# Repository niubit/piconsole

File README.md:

# PiConsole - Raspberry Pi Pico Retro Console

This repository has submodules. To clone add the `--recursive` option to the git clone command:

```
git clone --recursive https://github.com/niubit/piconsole.git
```

You can see a brief description (in spanish) in [this site](https://niubitbox.niubit.es/docs/niubitbox005/). A full description in english is available in [Instructables](https://www.instructables.com/PiConsole-Raspberry-Pi-Pico-Retro-Console/).

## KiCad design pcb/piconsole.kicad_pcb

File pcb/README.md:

Clonar con:

git clone --recursive git@bitbucket.org:niubit/piconsole_pcb.git

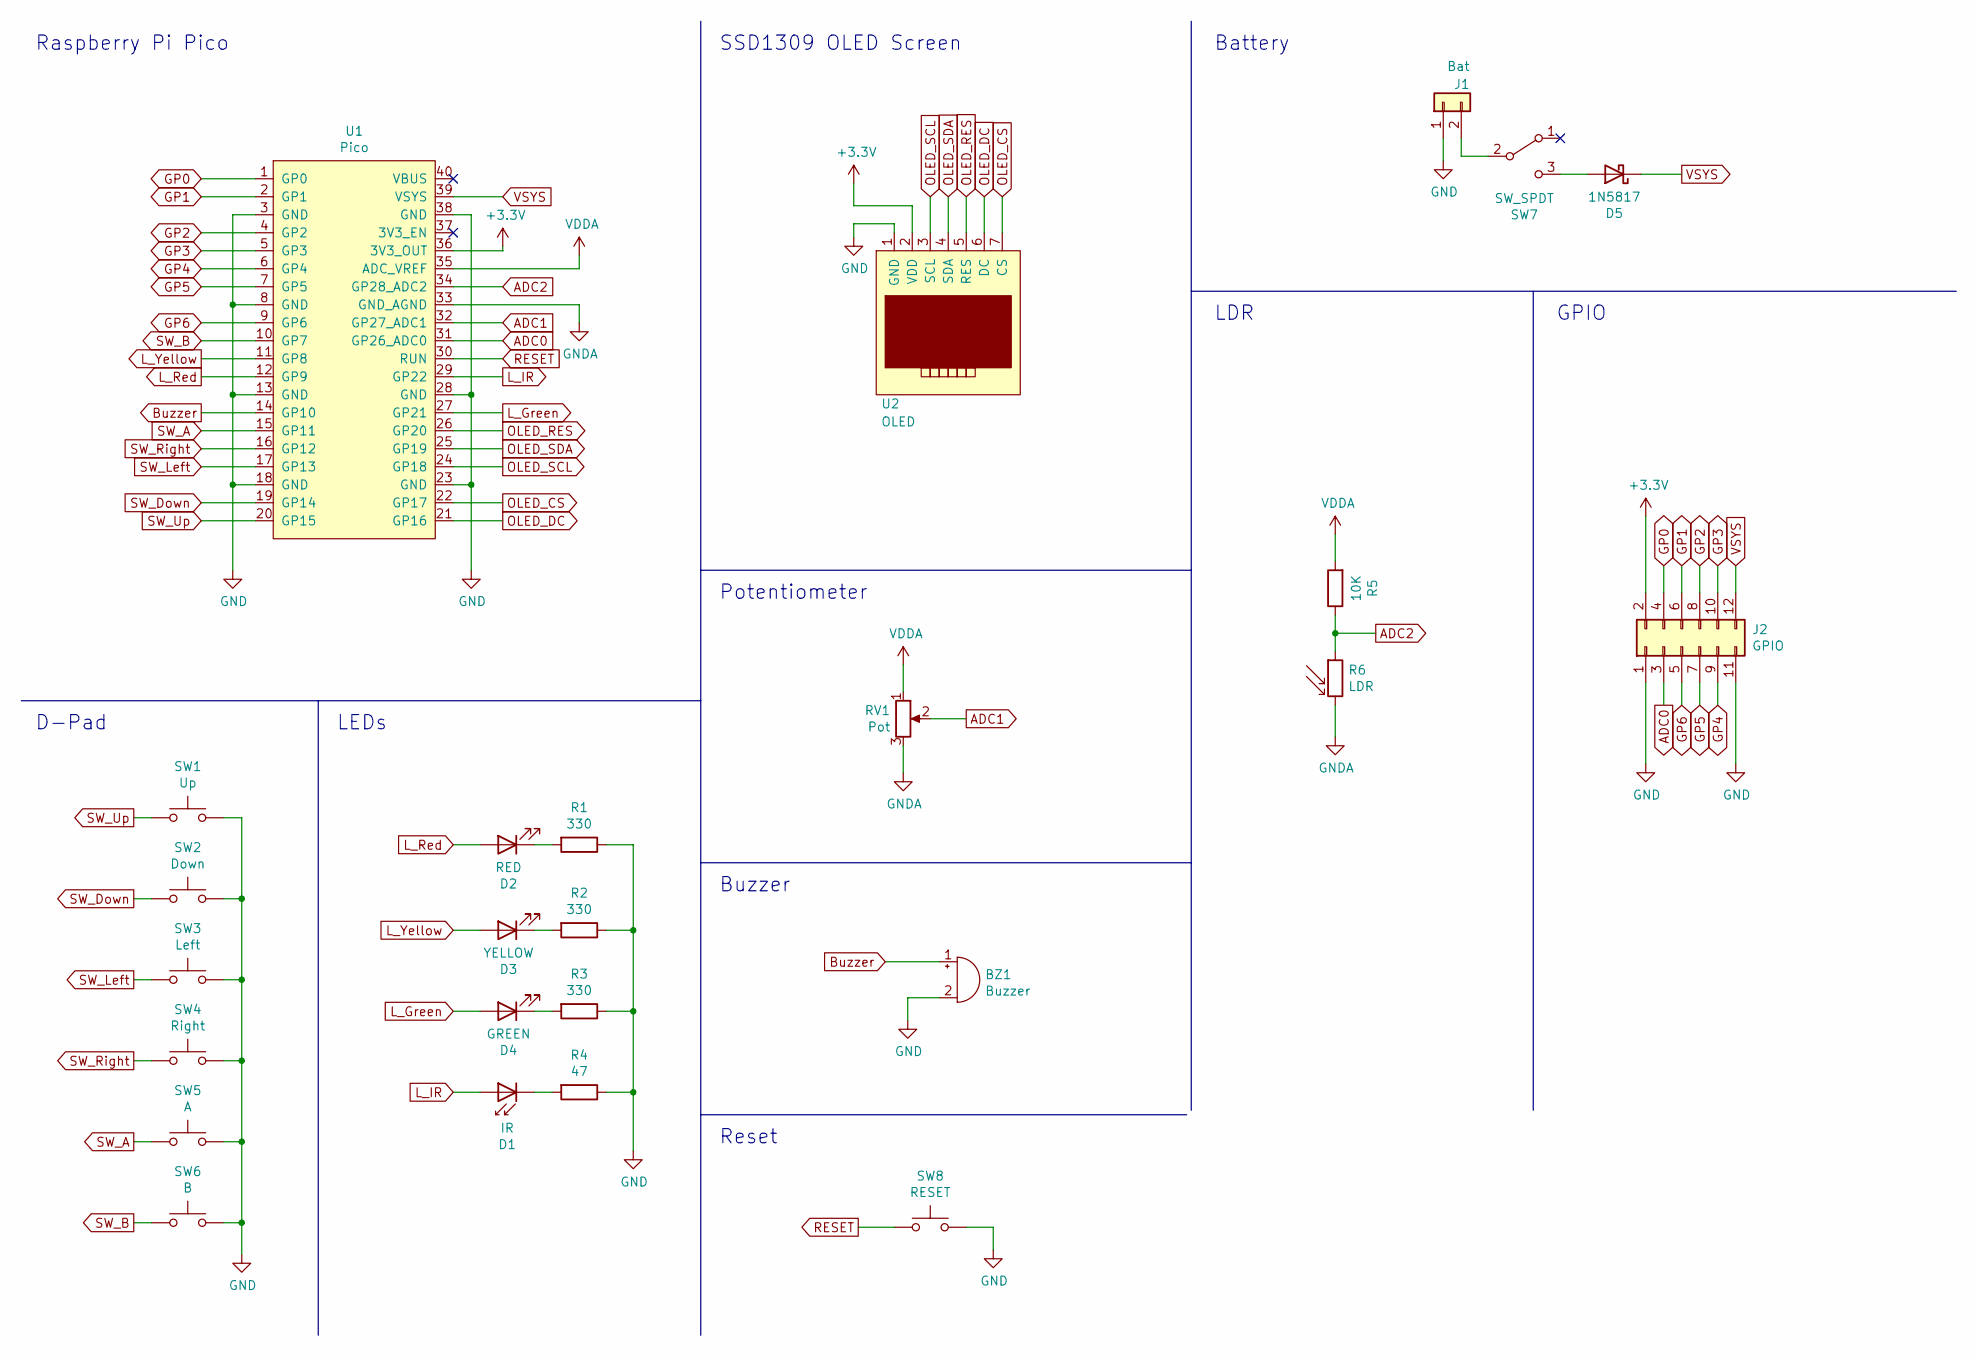
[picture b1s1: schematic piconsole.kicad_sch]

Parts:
BZ1: Buzzer; MagneticBuzzer_ProSignal_ABT-410-RC
D1: IR; LED_D5.0mm_IRGrey
D2: RED; LED_D5.0mm
D3: YELLOW; LED_D5.0mm
D4: GREEN; LED_D5.0mm
D5: 1N5817; D_DO-41_SOD81_P7.62mm_Horizontal
J1: Bat; PinHeader_1x02_P2.54mm_Vertical
J2: GPIO; PinSocket_2x06_P2.54mm_Horizontal
R1, R2, R3: 330; R_Axial_DIN0207_L6.3mm_D2.5mm_P10.16mm_Horizontal
R4: 47; R_Axial_DIN0207_L6.3mm_D2.5mm_P10.16mm_Horizontal
R5: 10K; R_Axial_DIN0207_L6.3mm_D2.5mm_P10.16mm_Horizontal
R6: LDR; R_LDR_5.0x4.1mm_P3mm_Vertical
RV1: Pot; Potentiometer_Alpha_RD901F-40-00D_Single_Vertical_mod
SW1: Up; SW_PUSH_8mm_2pin
SW2: Down; SW_PUSH_8mm_2pin
SW3: Left; SW_PUSH_8mm_2pin
SW4: Right; SW_PUSH_8mm_2pin
SW5: A; SW_PUSH_8mm_2pin
SW6: B; SW_PUSH_8mm_2pin
SW7: SW_SPDT; SW_SPDT_Angled
SW8: RESET; SW_PUSH_6mm
U1: Pico; raspberrypi-pico-module
U2: OLED; OLED-SSD1309-SPI

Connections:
+3V3: J2.2, U1.36 (3V3_OUT), U2.2 (VDD)
ADC0: J2.3, U1.31 (GP26_ADC0)
ADC1: RV1.2, U1.32 (GP27_ADC1)
ADC2: R5.1, R6.1, U1.34 (GP28_ADC2)
Buzzer: BZ1.1 (-), U1.14 (GP10)
GND: BZ1.2 (+), J1.1, J2.1, J2.11, R1.1, R2.1, R3.1, R4.1, SW1.2, SW2.2, SW3.2, SW4.2, SW5.2, SW6.2, SW8.2, U1.3 (GND), U1.8 (GND), U1.13 (GND), U1.18 (GND), U1.23 (GND), U1.28 (GND), U1.38 (GND), U2.1 (GND)
GNDA: R6.2, RV1.3, U1.33 (GND_AGND)
GP0: J2.4, U1.1 (GP0)
GP1: J2.6, U1.2 (GP1)
GP2: J2.8, U1.4 (GP2)
GP3: J2.10, U1.5 (GP3)
GP4: J2.9, U1.6 (GP4)
GP5: J2.7, U1.7 (GP5)
GP6: J2.5, U1.9 (GP6)
L_Green: D4.2 (A), U1.27 (GP21)
L_IR: D1.2 (A), U1.29 (GP22)
L_Red: D2.2 (A), U1.12 (GP9)
L_Yellow: D3.2 (A), U1.11 (GP8)
unnamed: D1.1 (K), R4.2
unnamed: D2.1 (K), R1.2
unnamed: D3.1 (K), R2.2
unnamed: D4.1 (K), R3.2
unnamed: D5.2 (A), SW7.3 (C)
unnamed: J1.2, SW7.2 (B)
OLED_CS: U1.22 (GP17), U2.7 (CS)
OLED_DC: U1.21 (GP16), U2.6 (DC)
OLED_RES: U1.26 (GP20), U2.5 (RES)
OLED_SCL: U1.24 (GP18), U2.3 (SCL)
OLED_SDA: U1.25 (GP19), U2.4 (SDA)
RESET: SW8.1, U1.30 (RUN)
SW_A: SW5.1, U1.15 (GP11)
SW_B: SW6.1, U1.10 (GP7)
SW_Down: SW2.1, U1.19 (GP14)
SW_Left: SW3.1, U1.17 (GP13)
SW_Right: SW4.1, U1.16 (GP12)
SW_Up: SW1.1, U1.20 (GP15)
VDDA: R5.2, RV1.1, U1.35 (ADC_VREF)
VSYS: D5.1 (K), J2.12, U1.39 (VSYS)

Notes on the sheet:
Buzzer
Potentiometer
LDR
Reset
LEDs
GPIO
D-Pad
SSD1309 OLED Screen
Raspberry Pi Pico
Battery

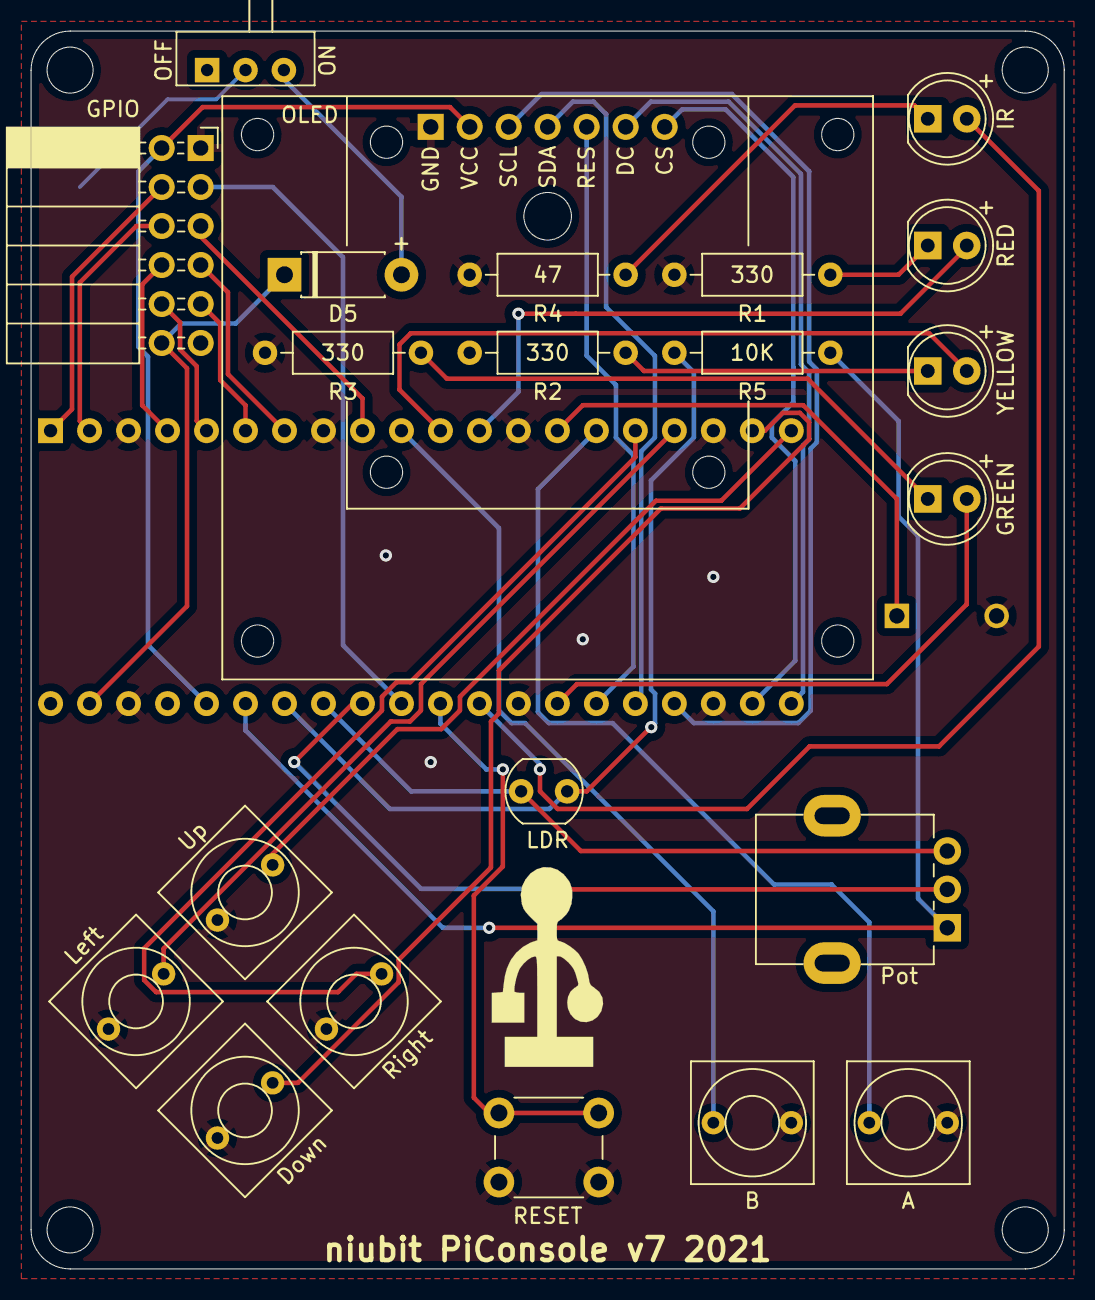
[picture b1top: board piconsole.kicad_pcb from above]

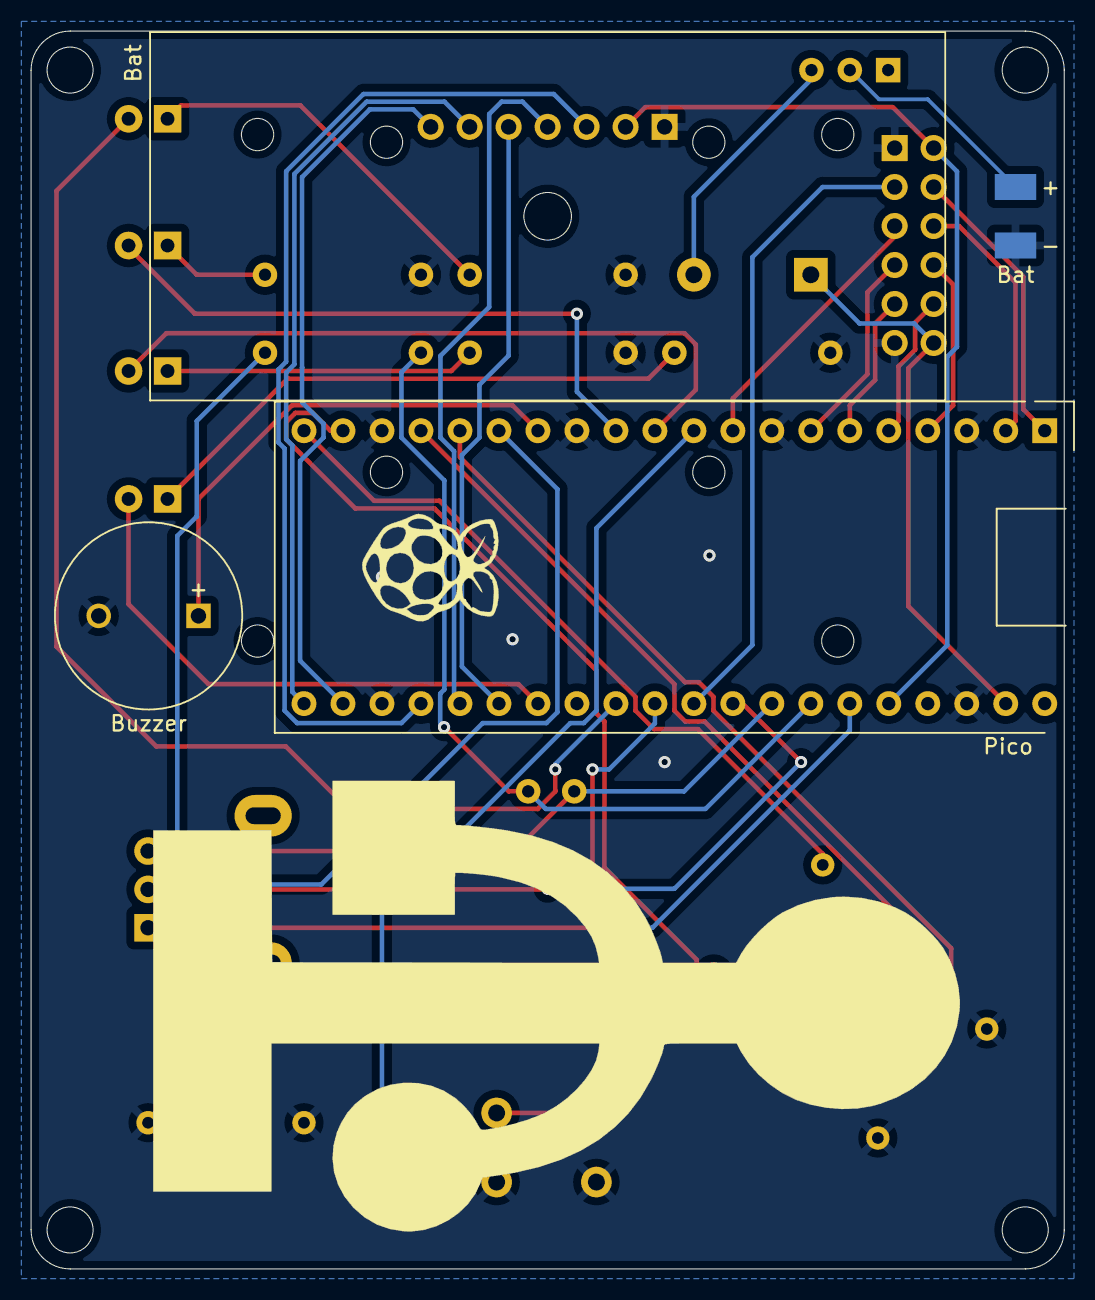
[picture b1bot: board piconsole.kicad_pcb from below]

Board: 2 copper layers, 67.3 x 80.6 mm, 25 parts (3 on the bottom side), 38 nets.

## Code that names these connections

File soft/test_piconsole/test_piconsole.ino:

#include <SPI.h>
#include <Wire.h>
#include <Adafruit_GFX.h>
#include <Adafruit_SSD1306.h>

#define SCREEN_WIDTH 128 // OLED display width, in pixels
#define SCREEN_HEIGHT 64 // OLED display height, in pixels

// Pins OLED
#define OLED_DC  16
#define OLED_CS  17
#define OLED_SCL 18
#define OLED_SDA 19
#define OLED_RES 20

// Pins LED
#define LED_YELLOW 8
#define LED_RED    9
#define LED_GREEN  21
#define LED_IR     22

// Pins Switch
#define SW_B     7
#define SW_A     11
#define SW_RIGHT 12
#define SW_LEFT  13
#define SW_DOWN  14
#define SW_UP    15

// Pins GPIO
#define GPIO_GP0     0
#define GPIO_GP1     1
#define GPIO_GP2     2
#define GPIO_GP3     3
#define GPIO_GP4     4
#define GPIO_GP5     5
#define GPIO_GP6     6
#define GPIO_ADC0    A0

// Pin Buzzer
#define BUZZER 10

// Pin Pot
#define POT_P A1

// Pin LDR
#define LDR_P A2

Adafruit_SSD1306 display(SCREEN_WIDTH, SCREEN_HEIGHT, OLED_SDA, OLED_SCL, OLED_DC, OLED_RES, OLED_CS);

// the setup function runs once when you press reset or power the board
void setup() {
  // initialize LED pins as output.
  pinMode(LED_BUILTIN, OUTPUT);
  pinMode(LED_YELLOW, OUTPUT);
  pinMode(LED_RED, OUTPUT);
  pinMode(LED_GREEN, OUTPUT);
  pinMode(LED_IR, OUTPUT);

  // initialize Switch pins as input.
  pinMode(SW_B, INPUT_PULLUP);
  pinMode(SW_A, INPUT_PULLUP);
  pinMode(SW_RIGHT, INPUT_PULLUP);
  pinMode(SW_LEFT, INPUT_PULLUP);
  pinMode(SW_DOWN, INPUT_PULLUP);
  pinMode(SW_UP, INPUT_PULLUP);


  // SSD1306_SWITCHCAPVCC = generate display voltage from 3.3V internally
  if(!display.begin(SSD1306_SWITCHCAPVCC)) {
    for(;;); // Don't proceed, loop forever
  }

  // Show initial display buffer contents on the screen --
  // the library initializes this with an Adafruit splash screen.
  display.display();
  delay(2000); // Pause for 2 seconds

  // Clear the buffer
  display.clearDisplay();
  display.display();
}

// the loop function runs over and over again forever
void loop() {
  digitalWrite(LED_IR, !digitalRead(SW_UP));
  digitalWrite(LED_RED, !digitalRead(SW_LEFT));
  digitalWrite(LED_YELLOW, !digitalRead(SW_RIGHT));
  digitalWrite(LED_GREEN, !digitalRead(SW_DOWN));
  tone(BUZZER, (!digitalRead(SW_A) || !digitalRead(SW_B) ? 1000 : 0));

  display.clearDisplay();
  display.setTextSize(1);      // Normal 1:1 pixel scale
  display.setTextColor(SSD1306_WHITE); // Draw white text
  display.cp437(true);         // Use full 256 char 'Code Page 437' font

  display.setCursor(0, 10);     // Start at top-left corner
  display.write("Pot:");
  display.drawRect(25, 8, 100, 10, SSD1306_WHITE);
  display.setCursor(0, 40);     // Start at top-left corner
  display.write("LDR:");
  display.drawRect(25, 38, 100, 10, SSD1306_WHITE);

  display.fillRect(25, 8, map(analogRead(POT_P), 0, 4096, 0, 100), 10, SSD1306_WHITE);
  display.fillRect(25, 38, map(analogRead(LDR_P), 0, 4096, 0, 100), 10, SSD1306_WHITE);
  display.display();
}

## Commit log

2021-08-20 Commit inicial.
2021-08-20 README a raíz.
2021-08-28 Avances carcasa.
2021-08-29 Avances.
2021-08-30 Corrección ruta repositorio en README.
2021-08-30 Tecla reset.
2021-08-30 Tecla reset más alta.
2021-08-31 Se agrandan ligeramente los agujeros de la PCB.
2021-09-01 Modificación altura labio tecla reset.
2021-09-01 Ajuste hueco pantalla.
2021-09-01 Tapa inferior.
2021-09-01 Recuperación de backup de juegos perdidos al unificar repositorios.
2021-09-02 Marcas en carcasa superior para pin 1 de GPIO y ON/OFF.
2021-09-07 Juego reflejos2 añadido.
2021-09-08 Leyenda para conector GPIO.
2021-10-01 Modelo 3D (step) de Raspberry Pi Pico.
2021-10-01 Colección de juegos de Thumby portada.
2021-10-01 Juegos Thumby en directorio
    Referencia a colección juegos Thumby en README. Limpieza formato ficheros código juegos.
2021-10-06 Datasheet de Adafruit para pantalla OLED SSD1306.
2021-10-06 Se añade librería SSD1306 a proyecto de 'CoderDojo_Twin_Cities'.
2021-10-06 Más detalle de directorio 'CoderDojo_Twin_Cities'.
2021-10-06 Mejoras colección cheungbx.
    Mejora en librería gameESP. Se sustituyen retornos de carro Windows por Linux.
2021-10-25 Directorio para juegos basados en Thumby.
2021-11-18 Carriles de los controles más altos y mejor sentados.
2021-11-19 Se agranda el espacio para el labio de los controles A y B.
2021-11-19 Más espacio para la cruceta.
2021-12-03 v7. Enrutado más directo a LED IR.
2021-12-17 Logo de niubit en carcasa inferior.
2021-12-17 Texto niubit en carcasa superior.
2021-12-20 STLs con logos niubit.
2021-12-20 Se traspasa el directorio 'soft' a un repo público.
2021-12-22 Logo niubit en carcasa inferior menos profundo.
2021-12-22 Enlace a repositorio de soft.
2021-12-23 Se recolocan referencias de algunos componentes.
    Bat y Pico para que no las oculten los propios componentes.
2022-01-04 Adaptado a KiCad 6.
2022-01-19 Nueva v7 (aún no se había fabricado)
2022-02-02 Se separa una via de un par
    Estaba demasiado próxima.
2022-02-03 Se ignoran backups
2022-02-03 Se borran backups
2022-03-14 Se adaptan rutas de modelos 3D componentes
2022-04-12 Public repository
2022-04-12 PiConsole render
2022-04-12 Minor changes
2022-04-12 Niubitbox site link
2022-04-12 Color in top and bottom case
2022-04-13 Soft directory
2022-04-13 Removing piconsole_soft
2022-04-29 CHIP-8 emulator added to soft
2022-06-10 Link to Instructables in README
2022-11-25 picotamachibi game added
